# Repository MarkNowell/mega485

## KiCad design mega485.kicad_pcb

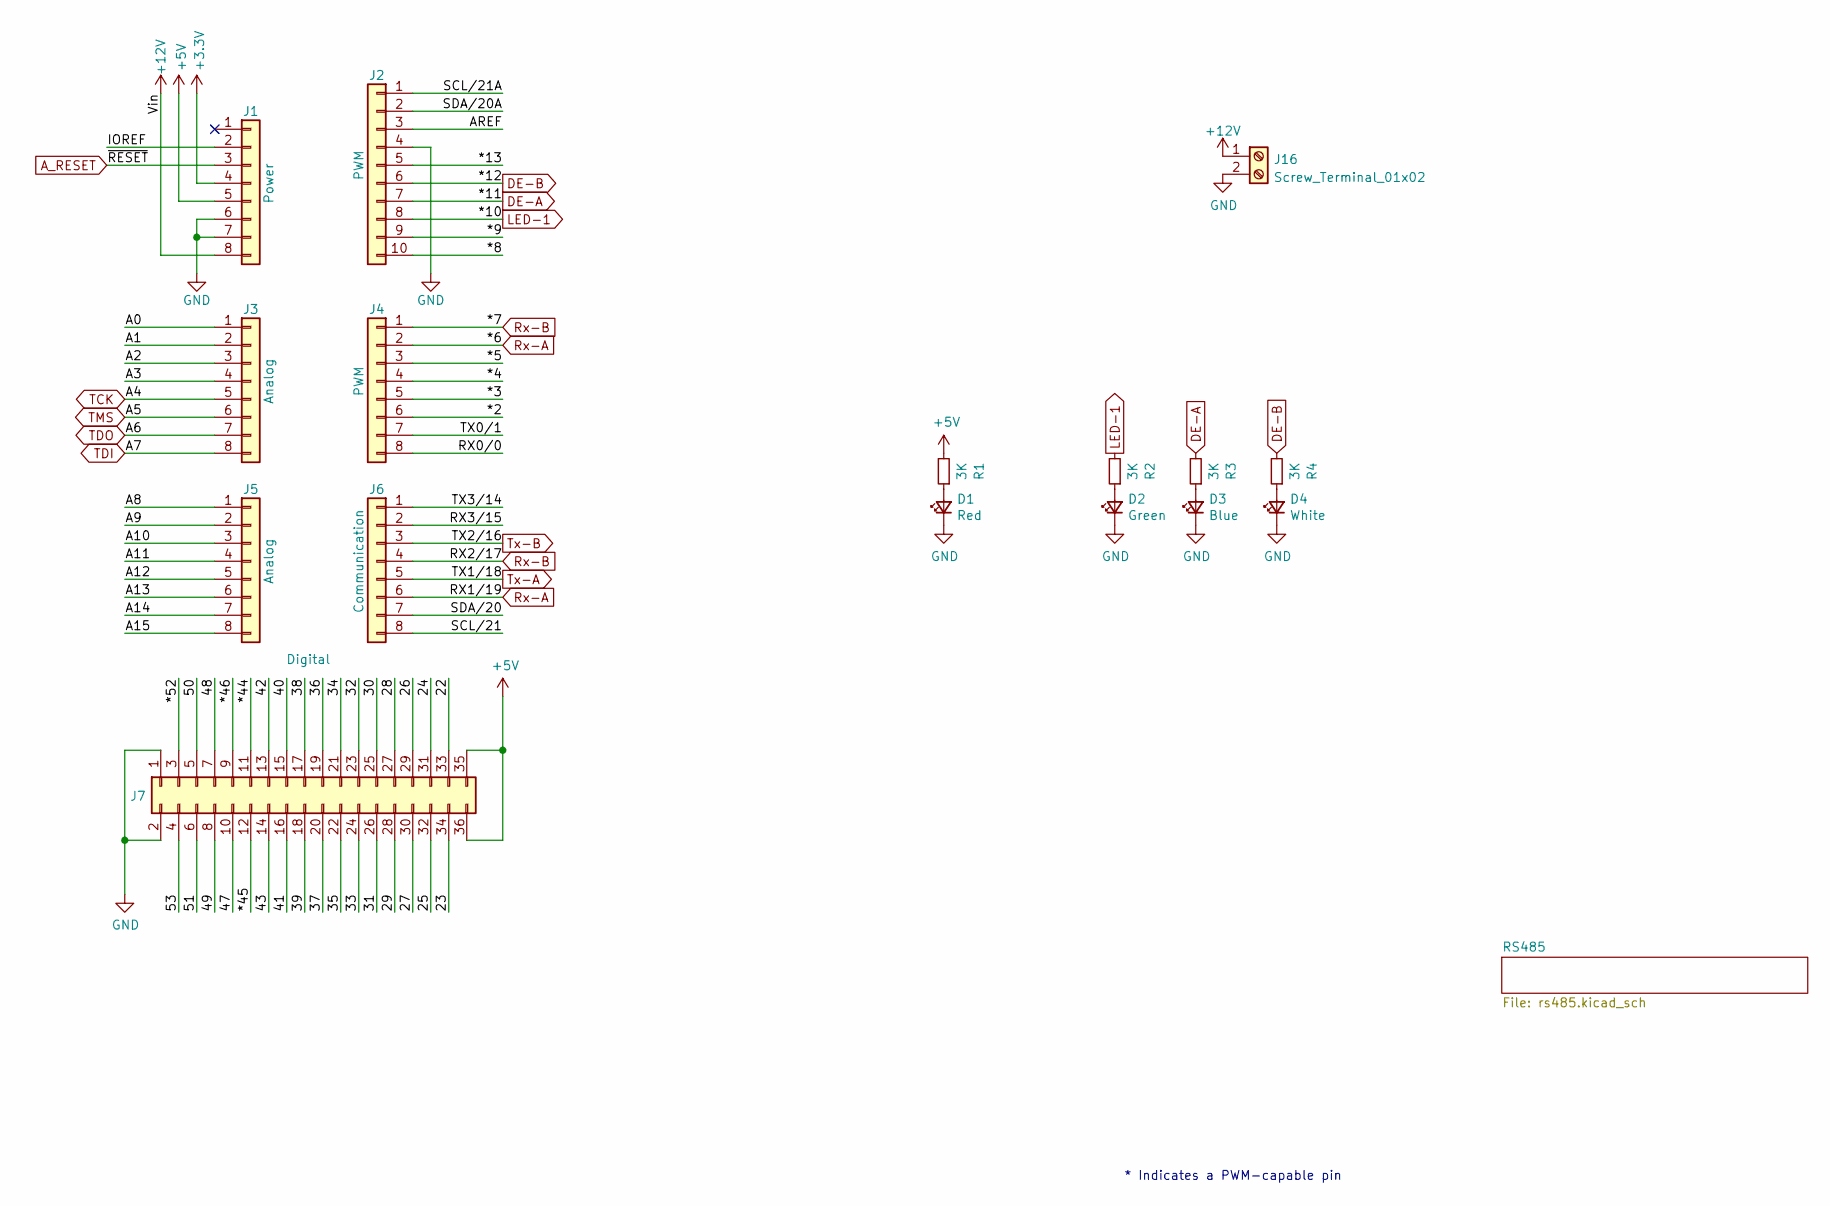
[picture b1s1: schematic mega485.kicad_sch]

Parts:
D1: Red; LED_0805_2012Metric; JLC C84256
D2: Green; LED_0805_2012Metric; JLC C2297
D3: Blue; LED_0805_2012Metric; JLC C2293
D4: White; LED_0805_2012Metric; JLC C34499
J1: Power; PinSocket_1x08_P2.54mm_Vertical
J2: PWM; PinSocket_1x10_P2.54mm_Vertical
J3, J5: Analog; PinSocket_1x08_P2.54mm_Vertical
J4: PWM; PinSocket_1x08_P2.54mm_Vertical
J6: Communication; PinSocket_1x08_P2.54mm_Vertical
J7: Digital; PinSocket_2x18_P2.54mm_Vertical
J16: Screw_Terminal_01x02; TerminalBlock_bornier-2_P5.08mm
R1, R2, R3, R4: 3K; R_0805_2012Metric; JLC C26010

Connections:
+3V3: J1.4
+5V: J1.5, J7.35, J7.36, R1.2; also elsewhere on the board
+12V: J1.8, J16.1
/22: J7.33
/23: J7.34
/24: J7.31
/25: J7.32
/26: J7.29
/27: J7.30
/28: J7.27
/29: J7.28
/30: J7.25
/31: J7.26
/32: J7.23
/33: J7.24
/34: J7.21
/35: J7.22
/36: J7.19
/37: J7.20
/38: J7.17
/39: J7.18
/40: J7.15
/41: J7.16
/42: J7.13
/43: J7.14
/47: J7.10
/48: J7.7
/49: J7.8
/50: J7.5
/51: J7.6
/53: J7.4
/*2: J4.6
/*3: J4.5
/*4: J4.4
/*5: J4.3
/*8: J2.10
/*9: J2.9
/*13: J2.5
/*44: J7.11
/*45: J7.12
/*46: J7.9
/*52: J7.3
/A0: J3.1
/A1: J3.2
/A2: J3.3
/A3: J3.4
/A8: J5.1
/A9: J5.2
/A10: J5.3
/A11: J5.4
/A12: J5.5
/A13: J5.6
/A14: J5.7
/A15: J5.8
/AREF: J2.3
/IOREF: J1.2
/RX0/0: J4.8
/RX3/15: J6.2
/SCL/21: J6.8
/SCL/21A: J2.1
/SDA/20: J6.7
/SDA/20A: J2.2
/TX0/1: J4.7
/TX3/14: J6.1
A_RESET: J1.3
DE-A: J2.7, R3.2; also elsewhere on the board
DE-B: J2.6, R4.2; also elsewhere on the board
GND: D1.1 (K), D2.1 (K), D3.1 (K), D4.1 (K), J1.6, J1.7, J2.4, J7.1, J7.2, J16.2; also elsewhere on the board
LED-1: J2.8, R2.2
unnamed: D1.2 (A), R1.1
unnamed: D2.2 (A), R2.1
unnamed: D3.2 (A), R3.1
unnamed: D4.2 (A), R4.1
Rx-A: J4.2, J6.6; also elsewhere on the board
Rx-B: J4.1, J6.4; also elsewhere on the board
TCK: J3.5
TDI: J3.8
TDO: J3.7
TMS: J3.6
Tx-A: J6.5; also elsewhere on the board
Tx-B: J6.3; also elsewhere on the board

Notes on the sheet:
* Indicates a PWM-capable pin

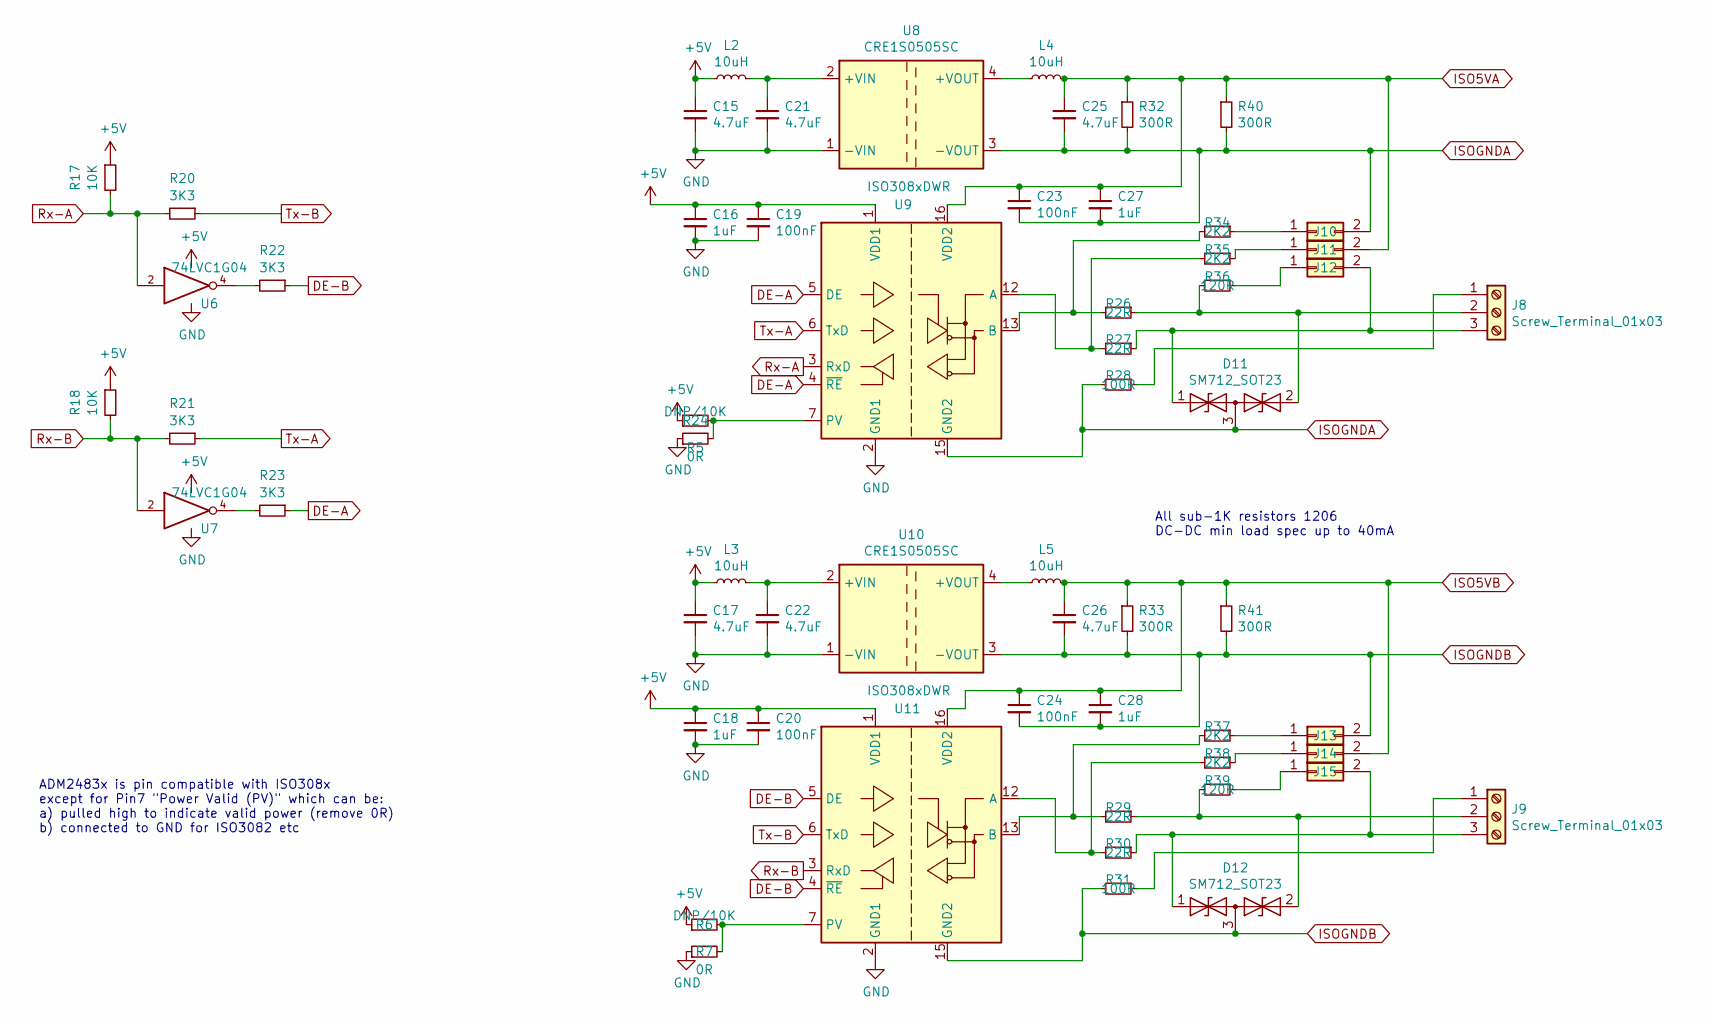
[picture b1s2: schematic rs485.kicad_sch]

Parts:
C15, C17, C21, C22, C25, C26: 4.7uF; C_1206_3216Metric; JLC C29823
C16, C18, C27, C28: 1uF; C_0603_1608Metric; JLC C15849
C19, C20, C23, C24: 100nF; C_0603_1608Metric; JLC C14663
D11, D12: SM712_SOT23; SOT-23; JLC C32677
J8, J9: Screw_Terminal_01x03; TerminalBlock_bornier-3_P5.08mm
J10, J11, J12, J13, J14, J15: Conn_02x01; PinHeader_1x02_P2.54mm_Vertical
L2, L3, L4, L5: 10uH; L_0805_2012Metric; JLC C1046
R5, R7: 0R; R_0805_2012Metric; JLC C17477
R6, R24: DNP/10K; R_0805_2012Metric; JLC-Alt C17414
R17, R18: 10K; R_0805_2012Metric; JLC C17414
R20, R21, R22, R23: 3K3; R_0805_2012Metric; JLC C26010
R26, R27, R29, R30: 22R; R_1206_3216Metric; JLC C17958
R28, R31: 100R; R_1206_3216Metric; JLC C17901
R32, R33, R40, R41: 300R; R_1206_3216Metric; JLC C17887
R34, R35, R37, R38: 2K2; R_0805_2012Metric; JLC C17520
R36, R39: 120R; R_1206_3216Metric; JLC C17909
U6, U7: 74LVC1G04; SOT-23-5; JLC C12509
U8, U10: CRE1S0505SC; Converter_DCDC_muRata_CRE1xxxxxxSC_THT
U9, U11: ISO308xDWR; SOIC-16W_7.5x10.3mm_P1.27mm; JLC C21710

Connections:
+5V: C15.1, C16.1, C17.1, C18.1, C19.1, C20.1, L2.1, L3.1, R6.1, R17.1, R18.1, R24.1, U6.5 (VCC), U7.5 (VCC), U9.1 (VDD1), U11.1 (VDD1); also elsewhere on the board
DE-A: R23.1, U9.4 (~RE), U9.5 (DE); also elsewhere on the board
DE-B: R22.1, U11.4 (~RE), U11.5 (DE); also elsewhere on the board
GND: C15.2, C16.2, C17.2, C18.2, C19.2, C20.2, C21.2, C22.2, R5.1, R7.1, U6.3 (GND), U7.3 (GND), U8.1 (-VIN), U9.2 (GND1), U9.8 (GND1), U10.1 (-VIN), U11.2 (GND1), U11.8 (GND1); also elsewhere on the board
ISO5VA: C23.1, C25.1, C27.1, J11.2, L4.2, R32.1, R40.1, U9.16 (VDD2)
ISO5VB: C24.1, C26.1, C28.1, J14.2, L5.2, R33.1, R41.1, U11.16 (VDD2)
ISOGNDA: C23.2, C25.2, C27.2, D11.3 (common), J10.2, R28.2, R32.2, R40.2, U8.3 (-VOUT), U9.9 (GND2), U9.15 (GND2)
ISOGNDB: C24.2, C26.2, C28.2, D12.3 (common), J13.2, R31.2, R33.2, R41.2, U10.3 (-VOUT), U11.9 (GND2), U11.15 (GND2)
unnamed: C21.1, L2.2, U8.2 (+VIN)
unnamed: C22.1, L3.2, U10.2 (+VIN)
unnamed: D11.1 (A1), J8.3, J12.2, R27.1
unnamed: D11.2 (A2), J8.2, R26.1, R36.2
unnamed: D12.1 (A1), J9.3, J15.2, R30.1
unnamed: D12.2 (A2), J9.2, R29.1, R39.2
unnamed: J8.1, R28.1
unnamed: J9.1, R31.1
unnamed: J10.1, R34.1
unnamed: J11.1, R35.1
unnamed: J12.1, R36.1
unnamed: J13.1, R37.1
unnamed: J14.1, R38.1
unnamed: J15.1, R39.1
unnamed: L4.1, U8.4 (+VOUT)
unnamed: L5.1, U10.4 (+VOUT)
unnamed: R6.2, R7.2, U11.7 (PV)
unnamed: R22.2, U6.4
unnamed: R23.2, U7.4
unnamed: R5.2, R24.2, U9.7 (PV)
unnamed: R26.2, R34.2, U9.13 (B)
unnamed: R27.2, R35.2, U9.12 (A)
unnamed: R29.2, R37.2, U11.13 (B)
unnamed: R30.2, R38.2, U11.12 (A)
Rx-A: R17.2, R20.2, U6.2, U9.3 (RxD); also elsewhere on the board
Rx-B: R18.2, R21.2, U7.2, U11.3 (RxD); also elsewhere on the board
Tx-A: R21.1, U9.6 (TxD); also elsewhere on the board
Tx-B: R20.1, U11.6 (TxD); also elsewhere on the board

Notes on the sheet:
ADM2483x is pin compatible with ISO308x except for Pin7 "Power Valid (PV)" which can be: a) pulled high to indicate valid power (remove 0R) b) connected to GND for ISO3082 etc
All sub-1K resistors 1206 DC-DC min load spec up to 40mA

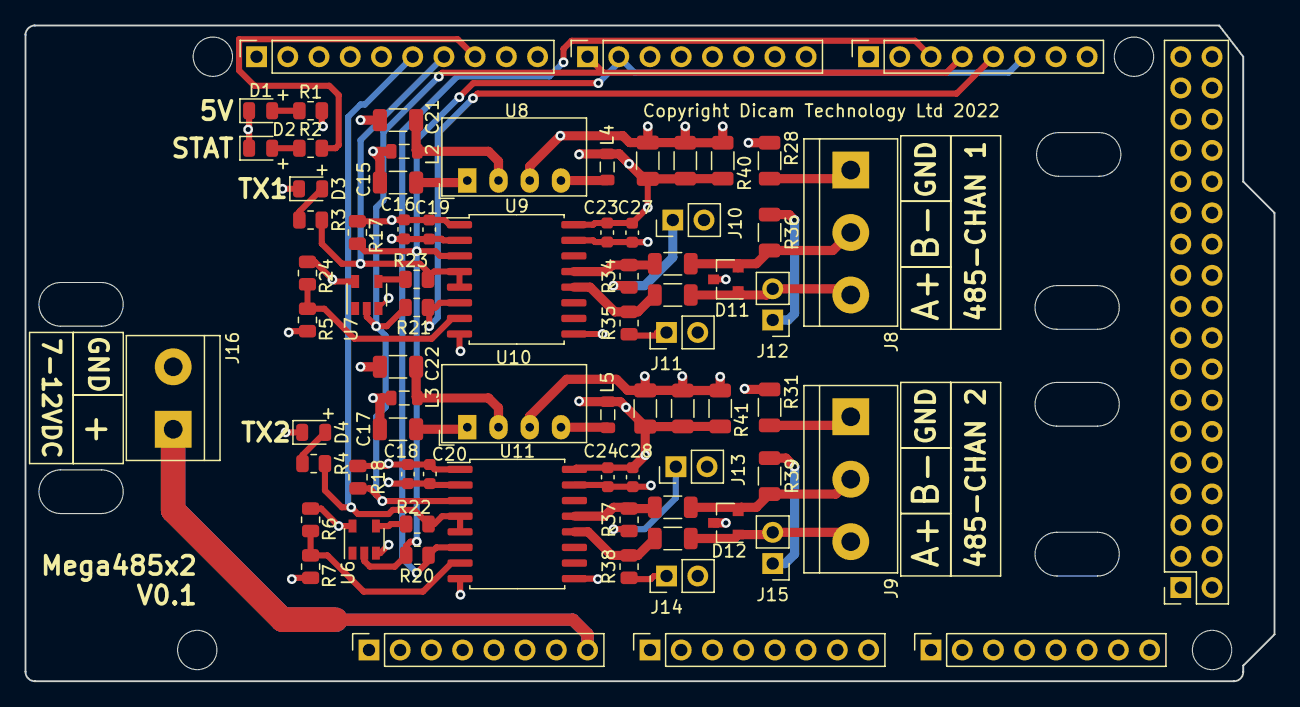
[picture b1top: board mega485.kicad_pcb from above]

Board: 4 copper layers, 101.6 x 53.3 mm, 80 parts (0 on the bottom side), 42 nets.

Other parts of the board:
MH1, MH2, MH5, MH6: MountingHole_3.2mm

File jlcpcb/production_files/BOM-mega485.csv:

Comment,Designator,Footprint,LCSC
10uH,"L2,L3,L4,L5",L_0805_2012Metric,C1046
74LVC1G04,"U6,U7",SOT-23-5,C12509
 100nF,"C19,C20,C23,C24",C_0603_1608Metric,C14663
1uF,"C16,C18,C27,C28",C_0603_1608Metric,C15849
10K,"R17,R18",R_0805_2012Metric,C17414
0R,"R5,R7",R_0805_2012Metric,C17477
2K2,"R34,R35,R37,R38",R_0805_2012Metric,C17520
300R,"R32,R33,R40,R41",R_1206_3216Metric,C17887
100R,"R28,R31",R_1206_3216Metric,C17901
120R,"R36,R39",R_1206_3216Metric,C17909
22R,"R26,R27,R29,R30",R_1206_3216Metric,C17958
ISO308xDWR,"U11,U9",SOIC-16W_7.5x10.3mm_P1.27mm,C21710
Blue,D3,LED_0805_2012Metric,C2293
Green,D2,LED_0805_2012Metric,C2297
3K,"R1,R2,R20,R21,R22,R23,R3,R4",R_0805_2012Metric,C26010
4.7uF,"C15,C17,C21,C22,C25,C26",C_1206_3216Metric,C29823
SM712_SOT23,"D11,D12",SOT-23,C32677
White,D4,LED_0805_2012Metric,C34499
Red,D1,LED_0805_2012Metric,C84256
Conn_02x01,J15,PinHeader_1x02_P2.54mm_Vertical,
Conn_02x01,J14,PinHeader_1x02_P2.54mm_Vertical,
Conn_02x01,J13,PinHeader_1x02_P2.54mm_Vertical,
Conn_02x01,J12,PinHeader_1x02_P2.54mm_Vertical,
Conn_02x01,J11,PinHeader_1x02_P2.54mm_Vertical,
Conn_02x01,J10,PinHeader_1x02_P2.54mm_Vertical,
DNP/10K,R6,R_0805_2012Metric,
Screw_Terminal_01x02,J16,TerminalBlock_bornier-2_P5.08mm,
Digital,J7,PinSocket_2x18_P2.54mm_Vertical,
Power,J1,PinSocket_1x08_P2.54mm_Vertical,
Analog,J3,PinSocket_1x08_P2.54mm_Vertical,
Analog,J5,PinSocket_1x08_P2.54mm_Vertical,
PWM,J2,PinSocket_1x10_P2.54mm_Vertical,
PWM,J4,PinSocket_1x08_P2.54mm_Vertical,
Communication,J6,PinSocket_1x08_P2.54mm_Vertical,
Screw_Terminal_01x03,J8,TerminalBlock_bornier-3_P5.08mm,
CRE1S0505SC,U10,Converter_DCDC_muRata_CRE1xxxxxxSC_THT,
DNP/10K,R24,R_0805_2012Metric,
CRE1S0505SC,U8,Converter_DCDC_muRata_CRE1xxxxxxSC_THT,
Screw_Terminal_01x03,J9,TerminalBlock_bornier-3_P5.08mm,

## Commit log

2022-11-29 Mega485 initial commit - design as per Nov22 JLC order with via errors on the 485 Chan1 block
2022-11-30 Fix incorrect connection between ISO5VA and ISOGNDA (fix associated planes in pcb)

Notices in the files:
mega485.kicad_pcb:
Copyright Dicam Technology Ltd 2022
